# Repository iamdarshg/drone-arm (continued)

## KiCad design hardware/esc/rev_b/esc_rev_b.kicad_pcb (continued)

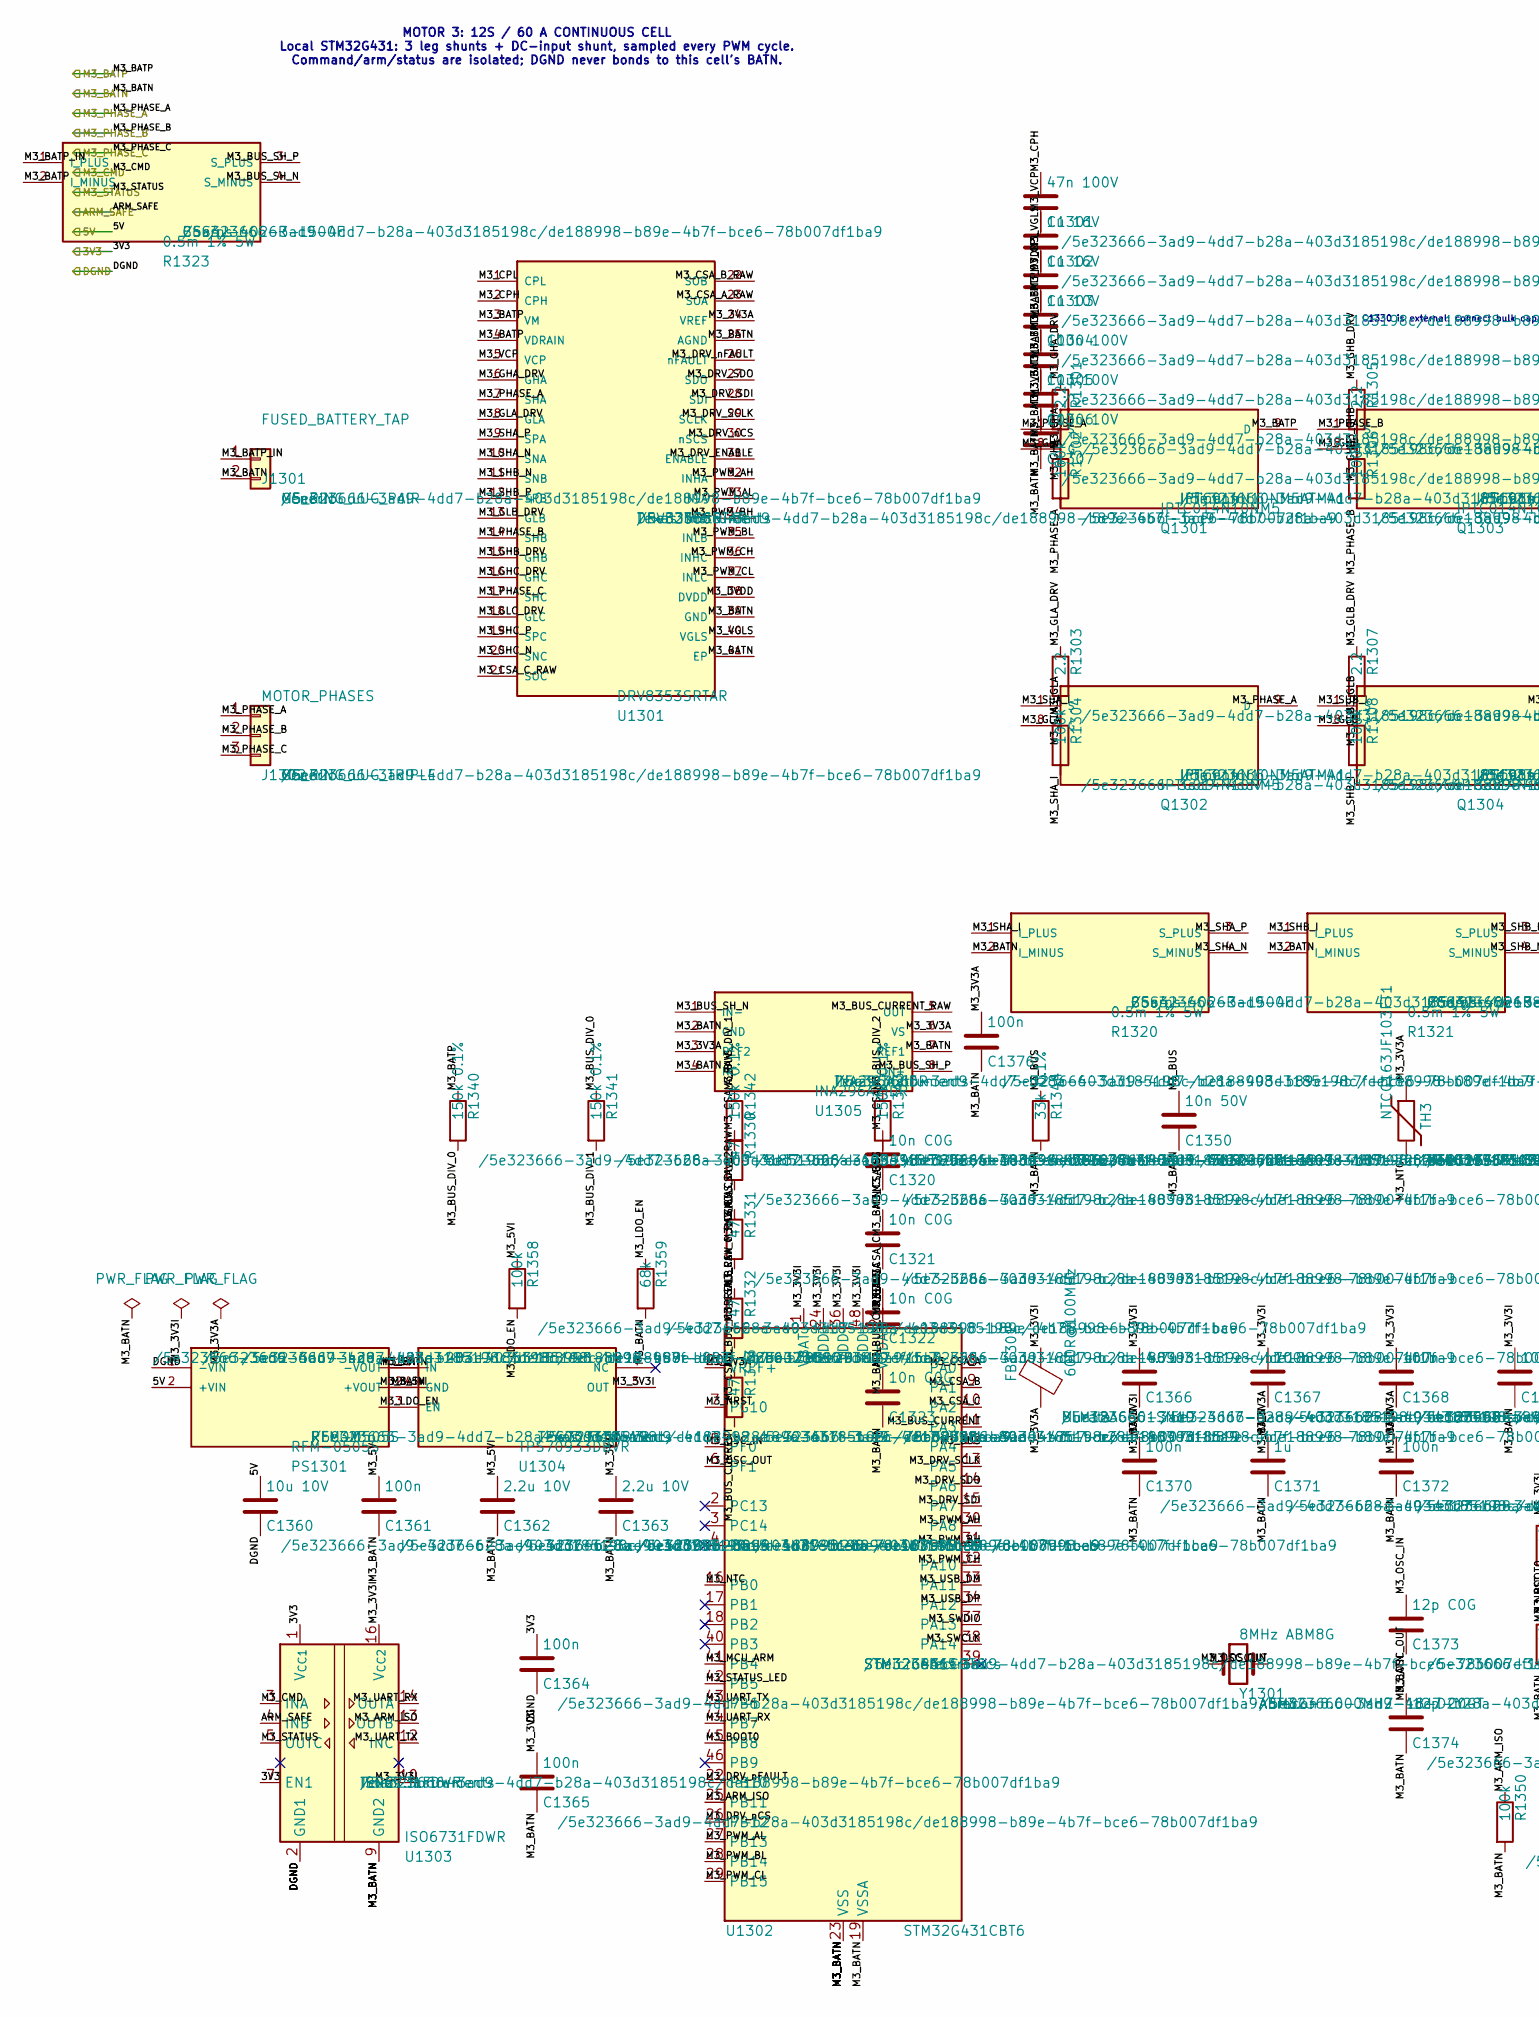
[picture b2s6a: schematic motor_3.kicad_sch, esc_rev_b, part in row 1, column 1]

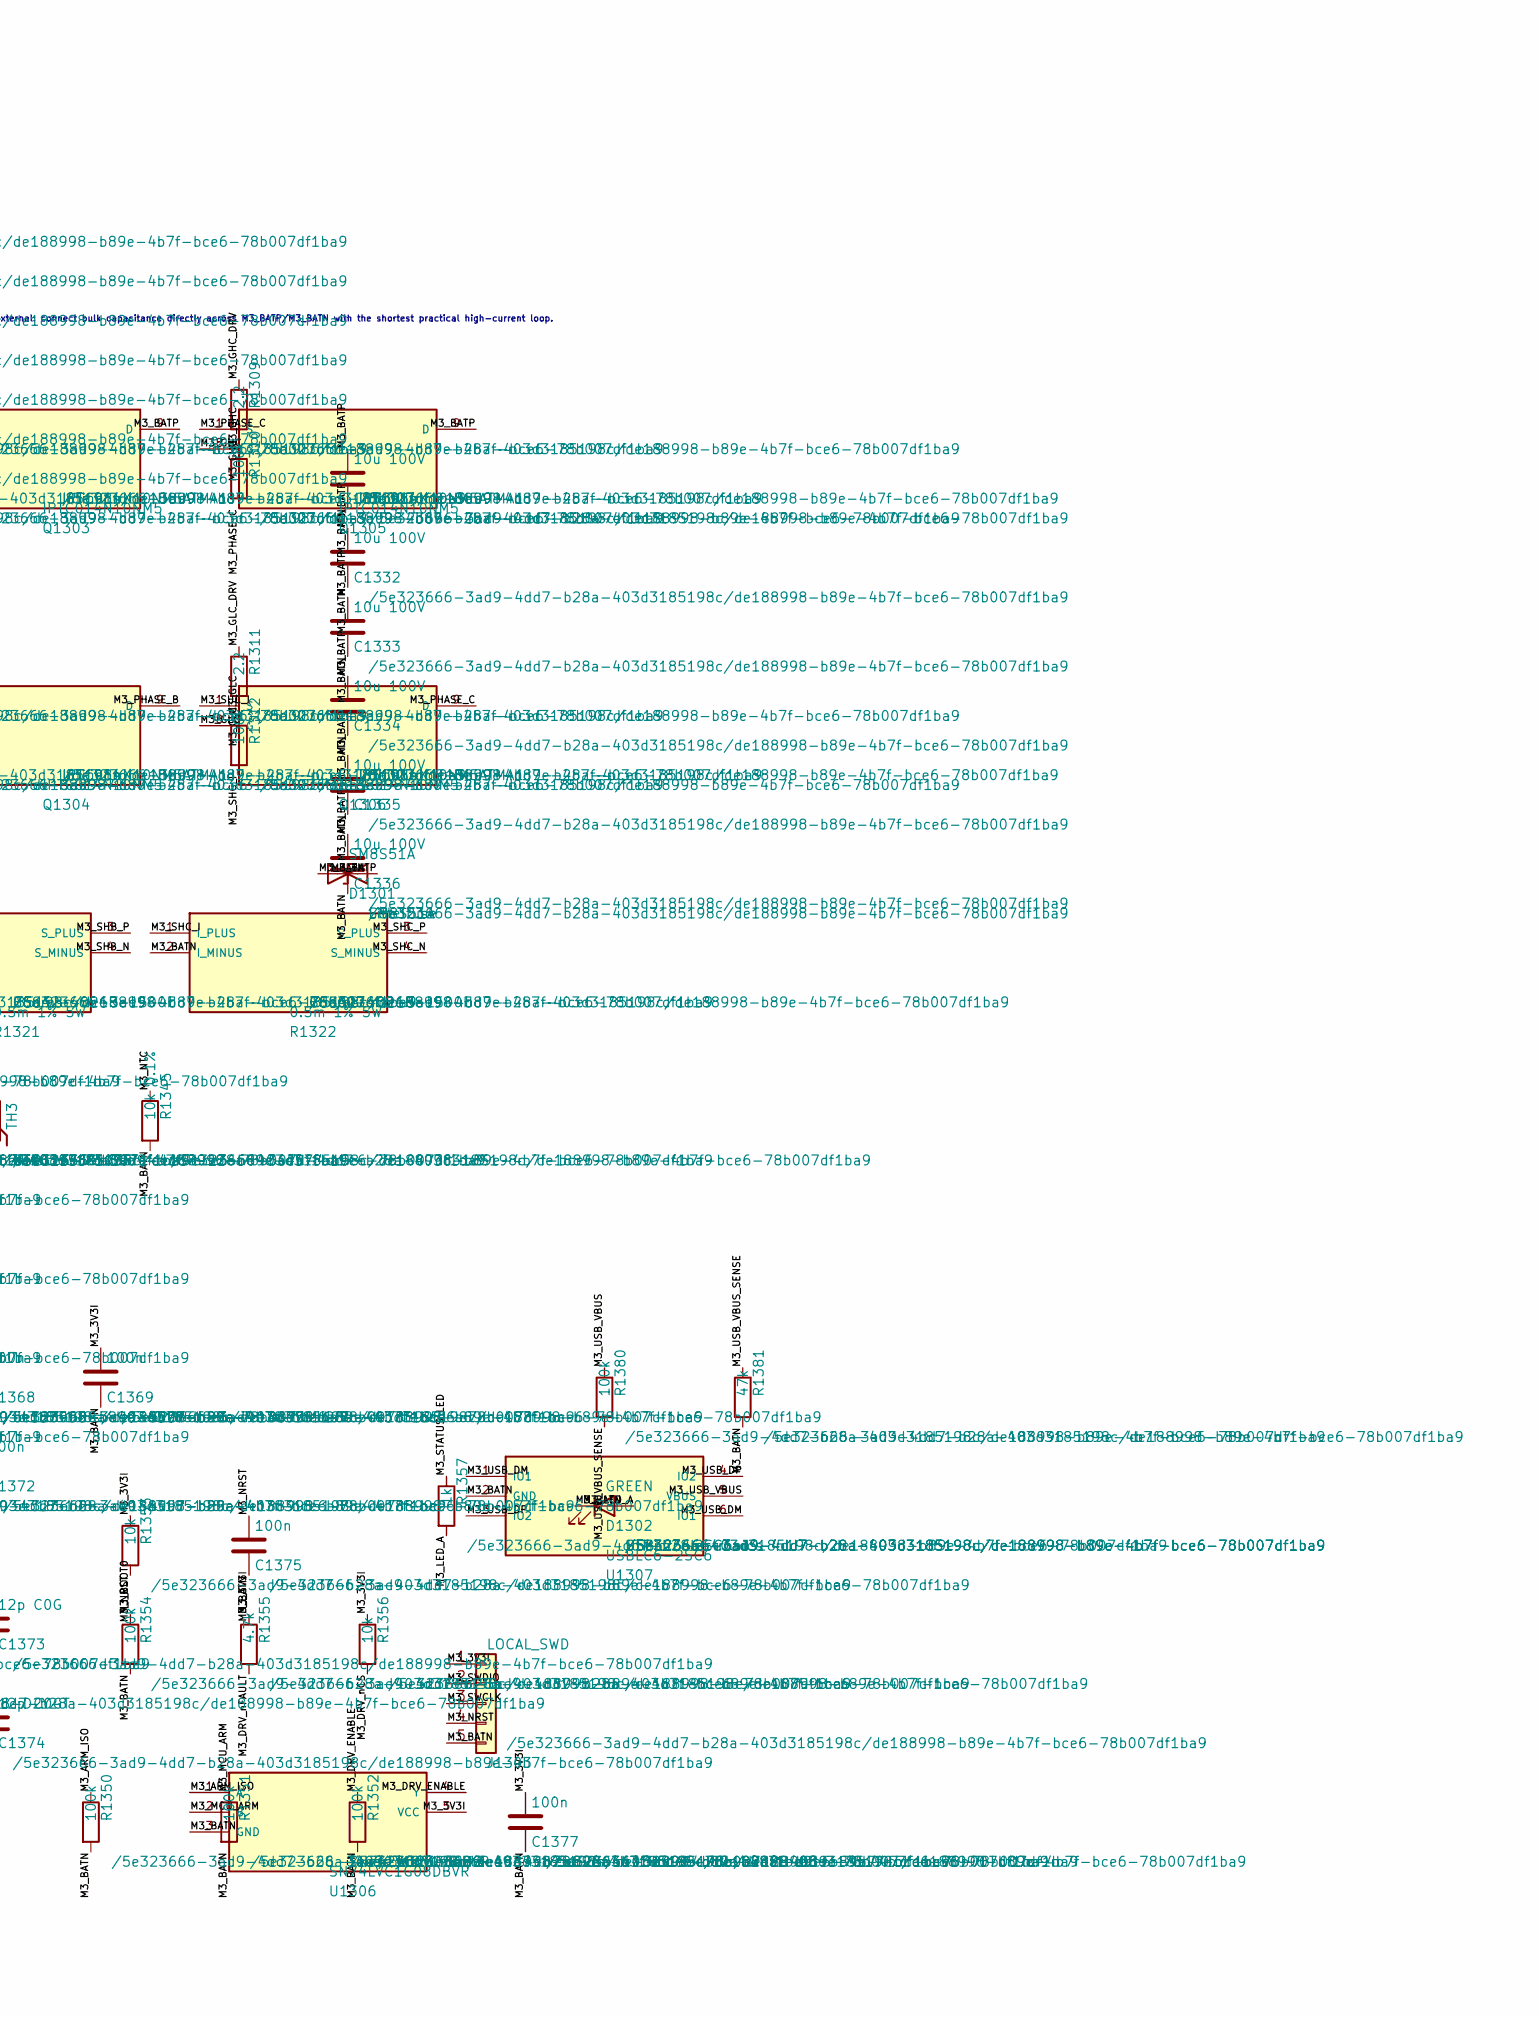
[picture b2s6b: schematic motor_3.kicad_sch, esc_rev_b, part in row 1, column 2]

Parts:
C1301: 47n 100V; C_0603_1608Metric
C1302, C1303: 1u 16V; C_0603_1608Metric
C1304: 1u 10V; C_0603_1608Metric
C1305: 100n 100V; C_0603_1608Metric
C1306, C1331, C1332, C1333, C1334, C1335, C1336: 10u 100V; C_1210_3225Metric
C1307: 100n 10V; C_0603_1608Metric
C1320, C1321, C1322, C1323: 10n C0G; C_0603_1608Metric
C1350: 10n 50V; C_0603_1608Metric
C1360: 10u 10V; C_0805_2012Metric
C1361, C1364, C1365, C1375, C1376, C1377: 100n; C_0603_1608Metric
C1362, C1363: 2.2u 10V; C_0603_1608Metric
C1366: 4.7u; C_0603_1608Metric
C1367, C1368, C1369, C1370, C1372: 100n; C_0402_1005Metric
C1371: 1u; C_0603_1608Metric
C1373, C1374: 12p C0G; C_0402_1005Metric
D1301: SM8S51A; DO-218AB_SM8S; MPN SM8S51A
D1302: GREEN; LED_0603_1608Metric
FB1301: 600R@100MHz; L_0603_1608Metric; MPN BLM18AG601SN1D
J1301: FUSED_BATTERY_TAP; POWER_LUG_M5_2P_P20; MPN M5_RING_LUG_PAIR
J1302: MOTOR_PHASES; POWER_LUG_M5_3P_P20; MPN M5_RING_LUG_TRIPLE
J1303: LOCAL_SWD; PinHeader_1x05_P1.27mm_Vertical
PS1301: RFM-0505S; RFM_SIP4_11.5x6_P2.54; MPN RFM-0505S
Q1301, Q1302, Q1303, Q1304, Q1305, Q1306: IPTC014N10NM5; PG-HDSOP-16_TOLT_IPTC; MPN IPTC014N10NM5ATMA1
R1301, R1303, R1305, R1307, R1309, R1311: 2.2; R_0603_1608Metric
R1302, R1304, R1306, R1308, R1310, R1312, R1350, R1351, R1352, R1354, R1358, R1380: 100k; R_0603_1608Metric
R1320, R1321, R1322, R1323: 0.5m 1% 5W; CSS4J-4026_Kelvin; MPN CSS4J-4026R-L500F
R1330, R1331, R1332, R1333: 47; R_0603_1608Metric
R1340, R1341, R1342, R1343: 150k 0.1%; R_1206_3216Metric
R1344: 33k 0.1%; R_0603_1608Metric
R1345: 10k 0.1%; R_0603_1608Metric
R1353, R1356: 10k; R_0603_1608Metric
R1355: 4.7k; R_0603_1608Metric
R1357: 1k; R_0603_1608Metric
R1359: 68k; R_0603_1608Metric
R1381: 47k; R_0603_1608Metric
TH3: NTCG163JF103FT1; R_0603_1608Metric; MPN NTCG163JF103FT1
U1301: DRV8353SRTAR; WQFN-40-EP_6x6_P0.5; MPN DRV8353SRTAR
U1302: STM32G431CBT6; LQFP-48_7x7mm_P0.5mm; MPN STM32G431CBT6
U1303: ISO6731FDWR; SOIC-16W_7.5x10.3mm_P1.27mm; MPN ISO6731FDWR
U1304: TPS70933DBVR; SOT-23-5; MPN TPS70933DBVR
U1305: INA296A2IDR; SOIC-8_3.9x4.9mm_P1.27mm; MPN INA296A2IDR
U1306: SN74LVC1G08DBVR; SOT-23-5; MPN SN74LVC1G08DBVR
U1307: USBLC6-2SC6; SOT-23-6; MPN USBLC6-2SC6
Y1301: 8MHz ABM8G; Crystal_SMD_3225-4Pin_3.2x2.5mm; MPN ABM8G-8.000MHZ-18-D2Y-T

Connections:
/3V3: C1364.1, U1303.1 (V_{CC1}), U1303.7 (EN1); also elsewhere on the board
/5V: C1360.1, PS1301.2 (+VIN); also elsewhere on the board
/ARM_SAFE: U1303.4 (INB); also elsewhere on the board
/DGND: C1360.2, C1364.2, PS1301.1 (-VIN), U1303.2 (GND1), U1303.8 (GND1); also elsewhere on the board
/M3_BATN: C1303.2, C1304.2, C1305.2, C1306.2, C1307.2, C1320.2, C1321.2, C1322.2, C1323.2, C1331.2, C1332.2, C1333.2, C1334.2, C1335.2, C1336.2, C1350.2, C1361.2, C1362.2, C1363.2, C1365.2, C1366.2, C1367.2, C1368.2, C1369.2, C1370.2, C1371.2, C1372.2, C1373.2, C1374.2, C1375.2, C1376.2, C1377.2, D1301.1 (A1), D1302.1 (K), J1301.2, J1303.5, PS1301.3 (-VOUT), R1320.2 (I_MINUS), R1321.2 (I_MINUS), R1322.2 (I_MINUS), R1344.2, R1345.2, R1350.2, R1351.2, R1352.2, R1354.2, R1359.2, R1381.2, U1301.25 (AGND), U1301.39 (GND), U1301.41 (EP), U1302.19 (VSSA), U1302.23 (VSS), U1302.35 (VSS), U1302.47 (VSS), U1303.9 (GND2), U1303.15 (GND2), U1304.2 (GND), U1305.2 (GND), U1305.4 (NC), U1305.7 (REF1), U1306.3 (GND), U1307.2 (GND); also elsewhere on the board
/M3_BATP: C1302.2, C1305.1, C1306.1, C1331.1, C1332.1, C1333.1, C1334.1, C1335.1, C1336.1, D1301.2 (A2), Q1301.9 (D), Q1303.9 (D), Q1305.9 (D), R1323.2 (I_MINUS), R1340.1, U1301.3 (VM), U1301.4 (VDRAIN); also elsewhere on the board
/M3_CMD: U1303.3 (INA); also elsewhere on the board
/M3_PHASE_A: J1302.1, Q1301.1 (S), Q1302.9 (D), R1302.2, U1301.7 (SHA)
/M3_PHASE_B: J1302.2, Q1303.1 (S), Q1304.9 (D), R1306.2, U1301.14 (SHB)
/M3_PHASE_C: J1302.3, Q1305.1 (S), Q1306.9 (D), R1310.2, U1301.17 (SHC)
/M3_STATUS: U1303.5 (OUTC); also elsewhere on the board
/Motor 3 power cell/M3_3V3A: C1307.1, C1371.1, C1372.1, C1376.1, FB1301.2, TH3.1, U1301.24 (VREF), U1302.20 (VREF+), U1302.21 (VDDA), U1305.3 (REF2), U1305.6 (VS)
/Motor 3 power cell/M3_3V3I: C1363.1, C1365.1, C1366.1, C1367.1, C1368.1, C1369.1, C1370.1, C1377.1, FB1301.1, J1303.1, R1353.1, R1355.1, R1356.1, U1302.1 (VBAT), U1302.24 (VDD), U1302.36 (VDD), U1302.48 (VDD), U1303.10 (EN2), U1303.16 (V_{CC2}), U1304.5 (OUT), U1306.5 (VCC)
/Motor 3 power cell/M3_5VI: C1361.1, C1362.1, PS1301.4 (+VOUT), R1358.1, U1304.1 (IN)
/Motor 3 power cell/M3_ARM_ISO: R1350.1, U1302.25 (PB11), U1303.13 (OUTB), U1306.1 (A)
/Motor 3 power cell/M3_BATP_IN: J1301.1, R1323.1 (I_PLUS)
/Motor 3 power cell/M3_BOOT0: R1354.1, U1302.45 (PB8)
/Motor 3 power cell/M3_BUS: C1350.1, R1343.2, R1344.1, U1302.12 (PA4)
/Motor 3 power cell/M3_BUS_CURRENT: C1323.1, R1333.2, U1302.11 (PA3)
/Motor 3 power cell/M3_BUS_CURRENT_RAW: R1333.1, U1305.5 (OUT)
/Motor 3 power cell/M3_BUS_DIV_0: R1340.2, R1341.1
/Motor 3 power cell/M3_BUS_DIV_1: R1341.2, R1342.1
/Motor 3 power cell/M3_BUS_DIV_2: R1342.2, R1343.1
/Motor 3 power cell/M3_BUS_SH_N: R1323.4 (S_MINUS), U1305.1 (IN-)
/Motor 3 power cell/M3_BUS_SH_P: R1323.3 (S_PLUS), U1305.8 (IN+)
/Motor 3 power cell/M3_CPH: C1301.1, U1301.2 (CPH)
/Motor 3 power cell/M3_CPL: C1301.2, U1301.1 (CPL)
/Motor 3 power cell/M3_CSA_A: C1320.1, R1330.2, U1302.8 (PA0)
/Motor 3 power cell/M3_CSA_A_RAW: R1330.1, U1301.23 (SOA)
/Motor 3 power cell/M3_CSA_B: C1321.1, R1331.2, U1302.9 (PA1)
/Motor 3 power cell/M3_CSA_B_RAW: R1331.1, U1301.22 (SOB)
/Motor 3 power cell/M3_CSA_C: C1322.1, R1332.2, U1302.10 (PA2)
/Motor 3 power cell/M3_CSA_C_RAW: R1332.1, U1301.21 (SOC)
/Motor 3 power cell/M3_DRV_ENABLE: R1352.1, U1301.31 (ENABLE), U1306.4 (Y)
/Motor 3 power cell/M3_DRV_SCLK: U1301.29 (SCLK), U1302.13 (PA5)
/Motor 3 power cell/M3_DRV_SDI: U1301.28 (SDI), U1302.15 (PA7)
/Motor 3 power cell/M3_DRV_SDO: U1301.27 (SDO), U1302.14 (PA6)
/Motor 3 power cell/M3_DRV_nCS: R1356.2, U1301.30 (nSCS), U1302.26 (PB12)
/Motor 3 power cell/M3_DRV_nFAULT: R1355.2, U1301.26 (nFAULT), U1302.22 (PB10)
/Motor 3 power cell/M3_DVDD: C1304.1, U1301.38 (DVDD)
/Motor 3 power cell/M3_GHA: Q1301.8 (G), R1301.2, R1302.1
/Motor 3 power cell/M3_GHA_DRV: R1301.1, U1301.6 (GHA)
/Motor 3 power cell/M3_GHB: Q1303.8 (G), R1305.2, R1306.1
/Motor 3 power cell/M3_GHB_DRV: R1305.1, U1301.15 (GHB)
/Motor 3 power cell/M3_GHC: Q1305.8 (G), R1309.2, R1310.1
/Motor 3 power cell/M3_GHC_DRV: R1309.1, U1301.16 (GHC)
/Motor 3 power cell/M3_GLA: Q1302.8 (G), R1303.2, R1304.1
/Motor 3 power cell/M3_GLA_DRV: R1303.1, U1301.8 (GLA)
/Motor 3 power cell/M3_GLB: Q1304.8 (G), R1307.2, R1308.1
/Motor 3 power cell/M3_GLB_DRV: R1307.1, U1301.13 (GLB)
/Motor 3 power cell/M3_GLC: Q1306.8 (G), R1311.2, R1312.1
/Motor 3 power cell/M3_GLC_DRV: R1311.1, U1301.18 (GLC)
/Motor 3 power cell/M3_LDO_EN: R1358.2, R1359.1, U1304.3 (EN)
/Motor 3 power cell/M3_LED_A: D1302.2 (A), R1357.2
/Motor 3 power cell/M3_MCU_ARM: R1351.1, U1302.41 (PB4), U1306.2 (B)
/Motor 3 power cell/M3_NRST: C1375.1, J1303.4, R1353.2, U1302.7 (PG10)
/Motor 3 power cell/M3_NTC: R1345.1, TH3.2, U1302.16 (PB0)
/Motor 3 power cell/M3_OSC_IN: C1373.1, U1302.5 (PF0), Y1301.1
/Motor 3 power cell/M3_OSC_OUT: C1374.1, U1302.6 (PF1), Y1301.2
/Motor 3 power cell/M3_PWM_AH: U1301.32 (INHA), U1302.30 (PA8)
/Motor 3 power cell/M3_PWM_AL: U1301.33 (INLA), U1302.27 (PB13)
/Motor 3 power cell/M3_PWM_BH: U1301.34 (INHB), U1302.31 (PA9)
/Motor 3 power cell/M3_PWM_BL: U1301.35 (INLB), U1302.28 (PB14)
/Motor 3 power cell/M3_PWM_CH: U1301.36 (INHC), U1302.32 (PA10)
/Motor 3 power cell/M3_PWM_CL: U1301.37 (INLC), U1302.29 (PB15)
/Motor 3 power cell/M3_SHA_I: Q1302.1 (S), R1304.2, R1320.1 (I_PLUS)
/Motor 3 power cell/M3_SHA_N: R1320.4 (S_MINUS), U1301.10 (SNA)
/Motor 3 power cell/M3_SHA_P: R1320.3 (S_PLUS), U1301.9 (SPA)
/Motor 3 power cell/M3_SHB_I: Q1304.1 (S), R1308.2, R1321.1 (I_PLUS)
/Motor 3 power cell/M3_SHB_N: R1321.4 (S_MINUS), U1301.11 (SNB)
/Motor 3 power cell/M3_SHB_P: R1321.3 (S_PLUS), U1301.12 (SPB)
/Motor 3 power cell/M3_SHC_I: Q1306.1 (S), R1312.2, R1322.1 (I_PLUS)
/Motor 3 power cell/M3_SHC_N: R1322.4 (S_MINUS), U1301.20 (SNC)
/Motor 3 power cell/M3_SHC_P: R1322.3 (S_PLUS), U1301.19 (SPC)
/Motor 3 power cell/M3_STATUS_LED: R1357.1, U1302.42 (PB5)
/Motor 3 power cell/M3_SWCLK: J1303.3, U1302.38 (PA14)
/Motor 3 power cell/M3_SWDIO: J1303.2, U1302.37 (PA13)
/Motor 3 power cell/M3_UART_RX: U1302.44 (PB7), U1303.14 (OUTA)
/Motor 3 power cell/M3_UART_TX: U1302.43 (PB6), U1303.12 (INC)
/Motor 3 power cell/M3_USB_DM: U1302.33 (PA11), U1307.1 (IO1), U1307.6 (IO1)
/Motor 3 power cell/M3_USB_DP: U1302.34 (PA12), U1307.3 (IO2), U1307.4 (IO2)
/Motor 3 power cell/M3_USB_VBUS: R1380.1, U1307.5 (VBUS)
/Motor 3 power cell/M3_USB_VBUS_SENSE: R1380.2, R1381.1
/Motor 3 power cell/M3_VCP: C1302.1, U1301.5 (VCP)
/Motor 3 power cell/M3_VGLS: C1303.1, U1301.40 (VGLS)

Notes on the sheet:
MOTOR 3: 12S / 60 A CONTINUOUS CELL Local STM32G431: 3 leg shunts + DC-input shunt, sampled every PWM cycle. Command/arm/status are isolated; DGND never bonds to this cell's BATN.
C1330 is external: connect bulk capacitance directly across M3_BATP/M3_BATN with the shortest practical high-current loop.
